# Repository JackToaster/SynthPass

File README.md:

# SynthPass

An open-source protocol & hardware design for to detect nose boops & transfer simple data, designed for protogen/synth fursuits.

Built to solve a very important problem. With SynthPass, you won't have to break character or pull off your paws and fumble with your phone to trade contact details. Just nose-boop, and SynthPass will automagically trade a small chunk of user-defined data, like a web link, username, or anything else that can fit in a couple hundred bytes of plain text. Then plug in your SynthPass at the end of the day and download all the data you've collected.

SynthPass is also designed to easily interface with nearly any protogen/synth fursuit. SynthPass hardware can be powered by a single 3.3V supply, and supports digital several digital interface options.

## Features

- ### Simple interface to fursuits
	- GPIO: pin HIGH (3.3V) when booped, LOW (0V) when not booped. Additional pin that's high
	- UART: Message for boop start/end
	- I2C: Register for boop status
    - Don't want to modify your firmware or connect the digital pins to your controller? The GPIO output can also drive an LED to indicate when another SynthPass is nearby and when a nose boop is detected.
- ### Advanced interface
	- UART/I2C Only
	- Approximate range & unique ID of peer prior to boop
	- Extra boop parameters (e.g. boop expression, color, name/species of peer)
- ### USB interface
    - Mass storage device for downloading collected data. Simply plug in the SynthPass into a computer and open `MESSAGES.HTM` in your web browser.
        - Edit the files `ME/BOOP.TXT` and `ME/PROX.TXT` to set your own messages to be transferred on proximity/boop
        - Edit `ME/SYNTHPAS.INI` to change settings for LED behavior, boop range, and enable proximity messages
    - Software bootloader switch for firmware updates over USB - send the character 'b' to the USB TTY that appears to switch to the USB bootloader.
## Hardware
SynthPass is based on the ultra-low-cost WCH CH57x series microcontrollers.
- ## 2.4GHz radio
	- Boop detection by RSSI (radio signal strength)
	- ISLER protocol for peer-to-peer and broadcast communication without need for pairing
	- CH572 also supports BLE (possibility for future companion app?)
- ## Protogen/Synth Suit Interface
	- 4-pin JST SH connector, compatible with QWIIC/Stemma QT (TODO?)
	- Single 3.3V input (possibly support 5V input with some hardware designs)
	- Option for I2C, UART, or GPIO communication protocol
	- Designed for easy integration with most synth/protogen heads

## Software
Using CH32Fun + iSLER library for communication

SynthPass communicates using BLE advertising frames with a fixed MAC address so that SynthPassdevices can easily be detected.

Communication (currently) uses a fixed channel (Channel 37) and PHY mode (1Mbps).

TODO document stuff better :3

## Development

**Building SynthPass**

SynthPass uses PlatformIO to manage the firmware toolchain, and the ch32fun framework to handle the ch572's hardware interfaces.

To compile the firmware, you'll need to:

- Clone the SynthPass repo `git clone https://github.com/JackToaster/SynthPass.git`
- Run `pio run -e [board hardware target]`. `[board hardware target]` should be replaced with one of the targets defined in `platformio.ini`:
  - `nanoch57x` for the nanoch57x dev board
  - `pretzelslab` for the SynthPass hardware in this repo & the SynthPasses handed out at Anthrocon 2026
  - `axionqc` for AxionQc's hardware design

**Updating firmware**

We have a custom upload script built into the PlatformIO configuration for SynthPass, all you need to do to update the firmware is:

`pio run -e [board target] -t upload`

for the "official" Pretzel's Lab hardware: `pio run -e pretzelslab -t upload`

If the firmware is borked and the flashing script doesn't work, hold down the boot button while plugging in the SynthPass to force it into ISP bootloader mode.

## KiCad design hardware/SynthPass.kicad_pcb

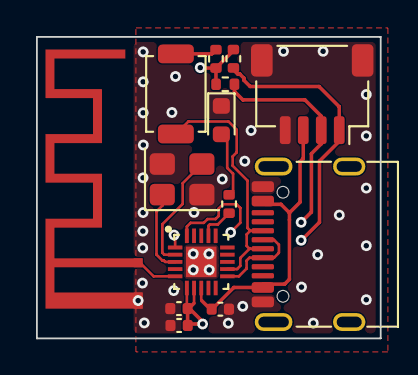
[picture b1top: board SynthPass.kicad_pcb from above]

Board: 4 copper layers, 19.1 x 16.8 mm, 14 parts (0 on the bottom side), 13 nets.

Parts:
AE1: PCB Antenna; Texas_SWRA117D_2.4GHz_Right
C1, C3: 10u; C_0402_1005Metric
C4: 0.1u; C_0402_1005Metric
D1: LED_Small; LED_0603_1608Metric
J1: SM04B-SRSS-TB; JST_SH_SM04B-SRSS-TB_1x04-1MP_P1.00mm_Horizontal
P1: USB_C_Plug_USB2.0; USB_C_Receptacle_G-Switch_GT-USB-7010ASV
R1, R2, R3, R4: 5.1k; R_0402_1005Metric
SW1: SW_Push; SW_SPST_TS-1088-xR020
U2: CH572D
Y2: 32MHz; Crystal_SMD_3225-4Pin_3.2x2.5mm

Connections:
+3V3: C3.1, C4.1, R1.2, R3.2, R4.2, U2.6 (VDD33), U2.7 (VIO33)
GND: AE1.2 (PCB_Trace), C1.2, C3.2, C4.2, D1.1 (K), J1.4, J1.MP (MountPin), P1.A1 (GND), P1.A12 (GND), P1.B1 (GND), P1.B12 (GND), U2.21 (GND/EPAD), Y2.2, Y2.4
unnamed: AE1.1 (FEED), U2.5 (ANT)
unnamed: D1.2 (A), R2.2
unnamed: R1.1, SW1.2
unnamed: R2.1, U2.17 (PA10/R6/T7)
unnamed: U2.3 (XI), Y2.1
unnamed: U2.2 (XO), Y2.3
SCL: J1.1, R3.1, U2.1 (PA3/T/R1/SCL2/SCK_/PWM3/CP0)
SDA: J1.2, R4.1, U2.20 (PA2/R/T1/SDA2/SCS_/PWM2/TMR1/CN)
UDM: P1.A7 (D-), P1.B7 (D-), U2.11 (PA0/UDM/R2/T3/SCL1)
UDP: P1.A6 (D+), P1.B6 (D+), SW1.1, U2.12 (PA1/UDP/R3/T2/SDA1)
VBUS: C1.1, J1.3, P1.A4 (VBUS), P1.A9 (VBUS), P1.B4 (VBUS), P1.B9 (VBUS), U2.8 (V5)

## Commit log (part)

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2026-01-30 protocol work
2026-01-30 fix readme not being the same
2026-02-08 PIO refactor cleanup
2026-02-08 Add WireShark plugin for dissecting synthpass packets
2026-02-22 Added USB Serial support
2026-05-27 work towards file handling on usb msc
2026-05-27 File storage change - single MD stream for messages + separate storage for attachment files
2026-05-28 Message store cleanup and bugfixes
2026-05-28 Trimming for utf-8
2026-06-24 working on boop to transfer data
2026-06-27 Add config, fix USB MSC issues, boop transfers data
2026-06-28 Add message deletion path
